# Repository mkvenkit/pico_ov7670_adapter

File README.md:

# pico_ov7670_adapter

An adapter PCB for using Pico 2W with an OV7670 camera module.

# License

<p xmlns:cc="http://creativecommons.org/ns#" xmlns:dct="http://purl.org/dc/terms/"><a property="dct:title" rel="cc:attributionURL" href="http://electronut.in">Pico 2 OV7670 Adapter PCB</a> by <a rel="cc:attributionURL dct:creator" property="cc:attributionName" href="http://electronut.in">Mahesh Venkitachalam</a> is licensed under <a href="https://creativecommons.org/licenses/by/4.0/?ref=chooser-v1" target="_blank" rel="license noopener noreferrer" style="display:inline-block;">CC BY 4.0</a></p>

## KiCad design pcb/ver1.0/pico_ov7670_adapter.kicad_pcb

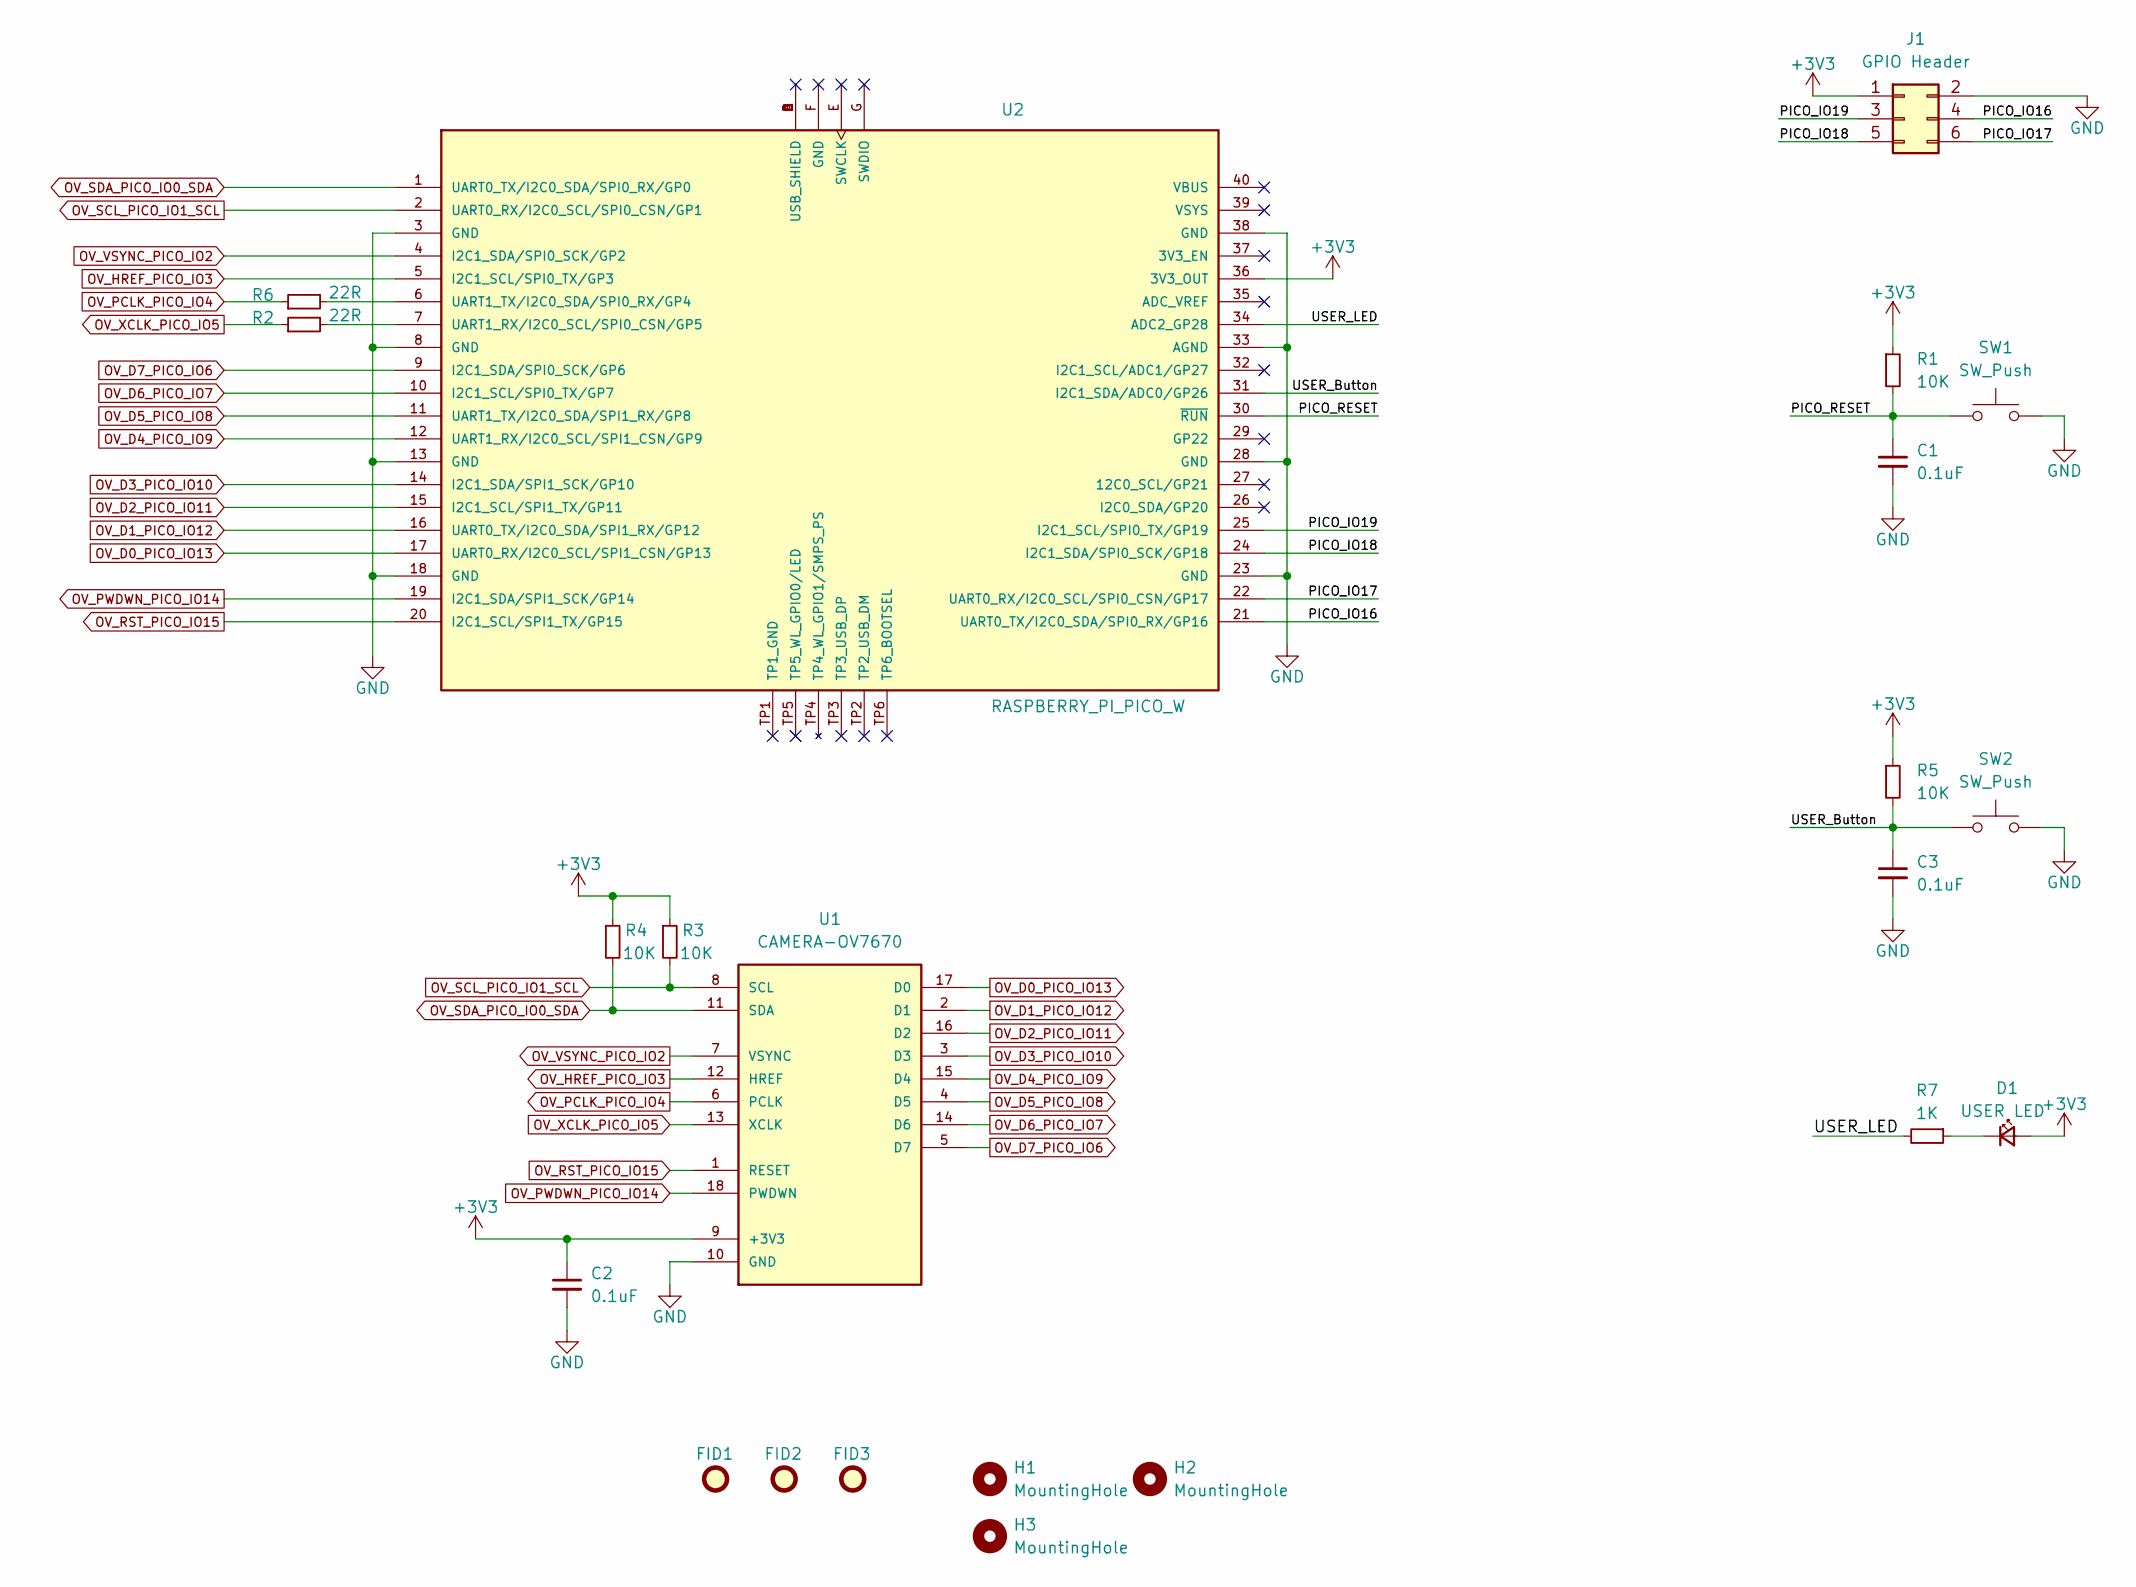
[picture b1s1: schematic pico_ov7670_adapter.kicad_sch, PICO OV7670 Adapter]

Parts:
C1, C2, C3: 0.1uF; C_0603_1608Metric
D1: USER LED; LED_0603_1608Metric
FID1, FID2, FID3: Fiducial; Fiducial_0.5mm_Mask1mm
H1, H2, H3: MountingHole; MountingHole_3.2mm_M3_DIN965
J1: GPIO Header; PinHeader_2x03_P2.54mm_Vertical
R1, R3, R4, R5: 10K; R_0603_1608Metric
R2, R6: 22R; R_0603_1608Metric
R7: 1K; R_0603_1608Metric
SW1, SW2: SW_Push; SW_SPST_PTS810
U1: CAMERA-OV7670; CAMERA-OV7670-DIP
U2: RASPBERRY_PI_PICO_W; PARTREV 2.4

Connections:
+3V3: C2.1, D1.2 (A), J1.1, R1.1, R3.1, R4.1, R5.1, U1.9 (+3V3), U2.36 (3V3_OUT)
/PICO_IO16: J1.4, U2.21 (UART0_TX/I2C0_SDA/SPI0_RX/GP16)
/PICO_IO17: J1.6, U2.22 (UART0_RX/I2C0_SCL/SPI0_CSN/GP17)
/PICO_IO18: J1.5, U2.24 (I2C1_SDA/SPI0_SCK/GP18)
/PICO_IO19: J1.3, U2.25 (I2C1_SCL/SPI0_TX/GP19)
/PICO_RESET: C1.1, R1.2, SW1.1, U2.30 (~RUN)
/USER_Button: C3.1, R5.2, SW2.1, U2.31 (I2C1_SDA/ADC0/GP26)
/USER_LED: R7.2, U2.34 (ADC2_GP28)
GND: C1.2, C2.2, C3.2, J1.2, SW1.2, SW2.2, U1.10 (GND), U2.3 (GND), U2.8 (GND), U2.13 (GND), U2.18 (GND), U2.23 (GND), U2.28 (GND), U2.33 (AGND), U2.38 (GND)
unnamed: D1.1 (K), R7.1
unnamed: R2.2, U2.7 (UART1_RX/I2C0_SCL/SPI0_CSN/GP5)
unnamed: R6.2, U2.6 (UART1_TX/I2C0_SDA/SPI0_RX/GP4)
OV_D0_PICO_IO13: U1.17 (D0), U2.17 (UART0_RX/I2C0_SCL/SPI1_CSN/GP13)
OV_D1_PICO_IO12: U1.2 (D1), U2.16 (UART0_TX/I2C0_SDA/SPI1_RX/GP12)
OV_D2_PICO_IO11: U1.16 (D2), U2.15 (I2C1_SCL/SPI1_TX/GP11)
OV_D3_PICO_IO10: U1.3 (D3), U2.14 (I2C1_SDA/SPI1_SCK/GP10)
OV_D4_PICO_IO9: U1.15 (D4), U2.12 (UART1_RX/I2C0_SCL/SPI1_CSN/GP9)
OV_D5_PICO_IO8: U1.4 (D5), U2.11 (UART1_TX/I2C0_SDA/SPI1_RX/GP8)
OV_D6_PICO_IO7: U1.14 (D6), U2.10 (I2C1_SCL/SPI0_TX/GP7)
OV_D7_PICO_IO6: U1.5 (D7), U2.9 (I2C1_SDA/SPI0_SCK/GP6)
OV_HREF_PICO_IO3: U1.12 (HREF), U2.5 (I2C1_SCL/SPI0_TX/GP3)
OV_PCLK_PICO_IO4: R6.1, U1.6 (PCLK)
OV_PWDWN_PICO_IO14: U1.18 (PWDWN), U2.19 (I2C1_SDA/SPI1_SCK/GP14)
OV_RST_PICO_IO15: U1.1 (RESET), U2.20 (I2C1_SCL/SPI1_TX/GP15)
OV_SCL_PICO_IO1_SCL: R3.2, U1.8 (SCL), U2.2 (UART0_RX/I2C0_SCL/SPI0_CSN/GP1)
OV_SDA_PICO_IO0_SDA: R4.2, U1.11 (SDA), U2.1 (UART0_TX/I2C0_SDA/SPI0_RX/GP0)
OV_VSYNC_PICO_IO2: U1.7 (VSYNC), U2.4 (I2C1_SDA/SPI0_SCK/GP2)
OV_XCLK_PICO_IO5: R2.1, U1.13 (XCLK)

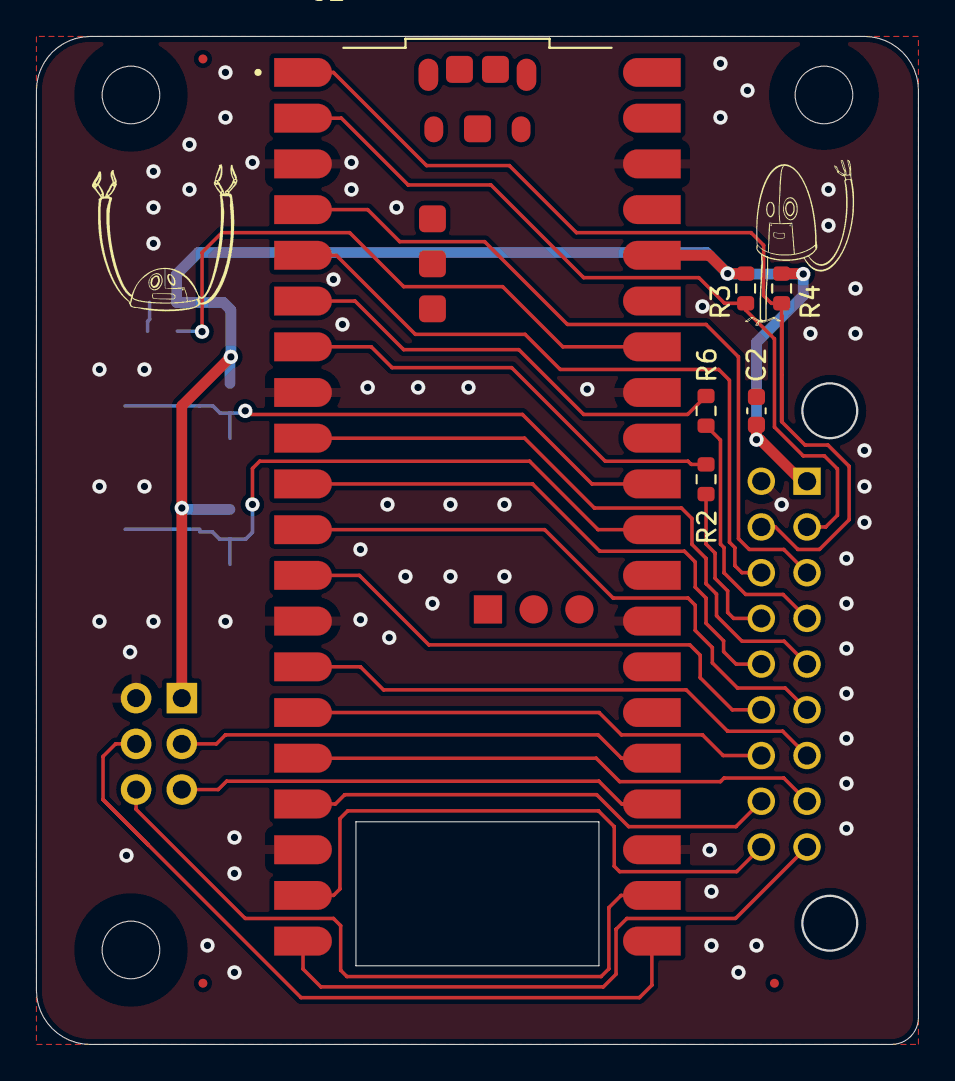
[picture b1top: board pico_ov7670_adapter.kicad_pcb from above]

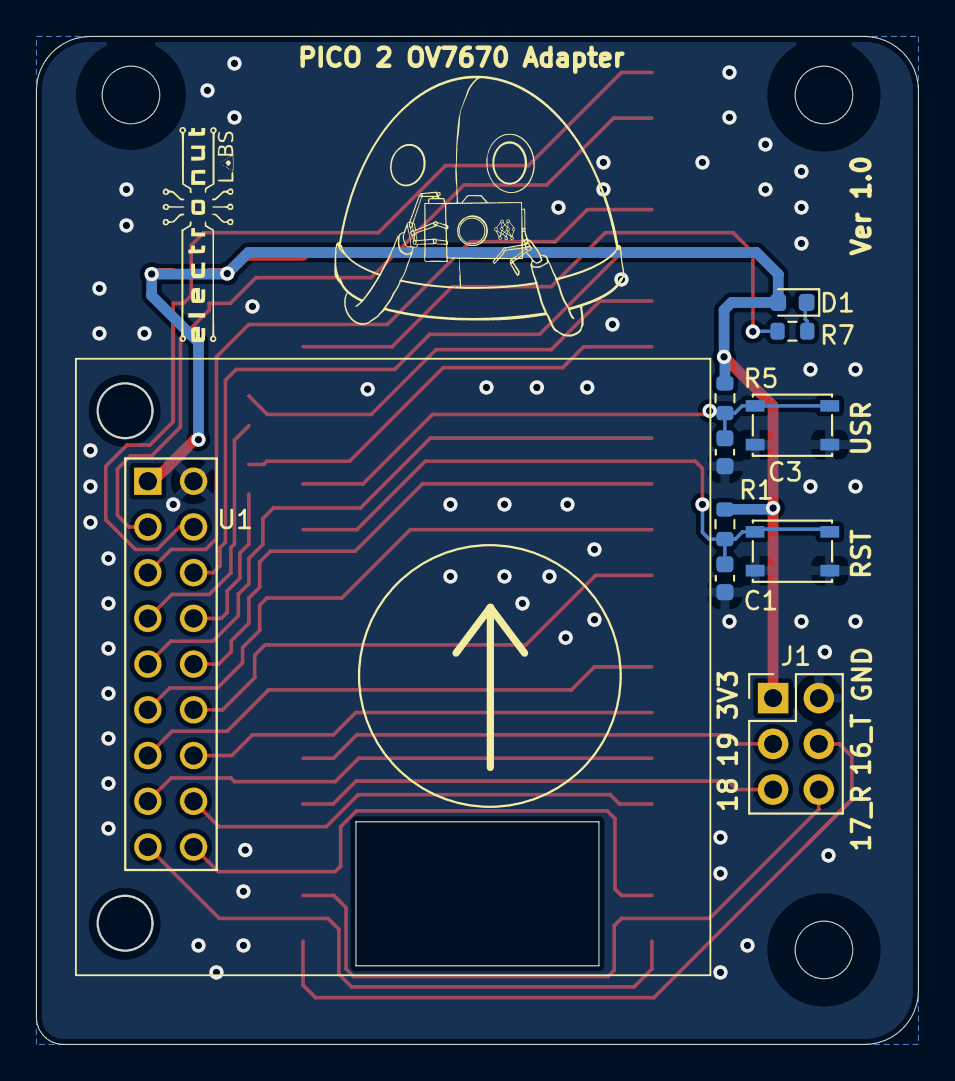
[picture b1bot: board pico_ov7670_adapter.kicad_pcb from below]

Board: 2 copper layers, 48.9 x 55.9 mm, 22 parts (10 on the bottom side), 28 nets.

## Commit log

2024-12-30 adding basic documents
2024-12-30 started
2025-01-02 basic schematic and layout updated
2025-01-05 footprints updated
2025-01-05 rp2350 datasheet added
2025-01-05 layout updated
2025-01-06 basic routing completed
2025-01-07 routing completed
2025-01-09 art work updated in PCB
2025-01-11 via stitching added
2025-01-12 updated layout changes as per the feedback.
2025-01-14 layout updated.
2025-01-14 adding code
2025-01-17 layout updated as per the feedback.
2025-01-18 basic rotuing completed
2025-01-18 GPIO header change updated
2025-01-18 gerber files added
2025-01-28 schematic pdf updated
2025-01-29 adding framegrabber
2025-01-29 I2C detected camera!
2025-01-30 clean up
2025-01-30 Refactoring
2025-01-30 I2c write works, QVGA configured
2025-01-30 height is correct QVGA 240 px
2025-01-31 found PCLK scaling reg
2025-01-31 pclk scale works
2025-02-02 sending image over uart
2025-02-03 Generated code for test image and PIO/DMA
2025-02-03 Added button and LED
2025-02-03 Hooking up DMA + PIO
2025-02-03 dma tested
2025-02-04 getting something
2025-02-04 capturing something
2025-02-04 color bar
2025-02-04 using row width from TX FIFO
2025-02-04 something
2025-02-04 rev bits
2025-02-05 added raw
2025-02-05 tested transfer using 0xCB
2025-02-05 added linux driver code
2025-02-06 PWM peripheral works
2025-02-06 Moved to pio0
2025-02-08 Updated docs
2025-02-11 Trying a simple loop
2025-02-11 flip image
2025-02-11 faster access to gpio
2025-02-11 Experimenting
2025-02-11 ver1.0 started
2025-02-12 wait syntax wrong
    wait 1 gpio 4 works!
2025-02-12 Added YUV config from app note
2025-02-13 Y channel works
2025-02-16 Added test bar - works
2025-02-20 camera module footptint updated.
2025-02-20 removed old gerber files
